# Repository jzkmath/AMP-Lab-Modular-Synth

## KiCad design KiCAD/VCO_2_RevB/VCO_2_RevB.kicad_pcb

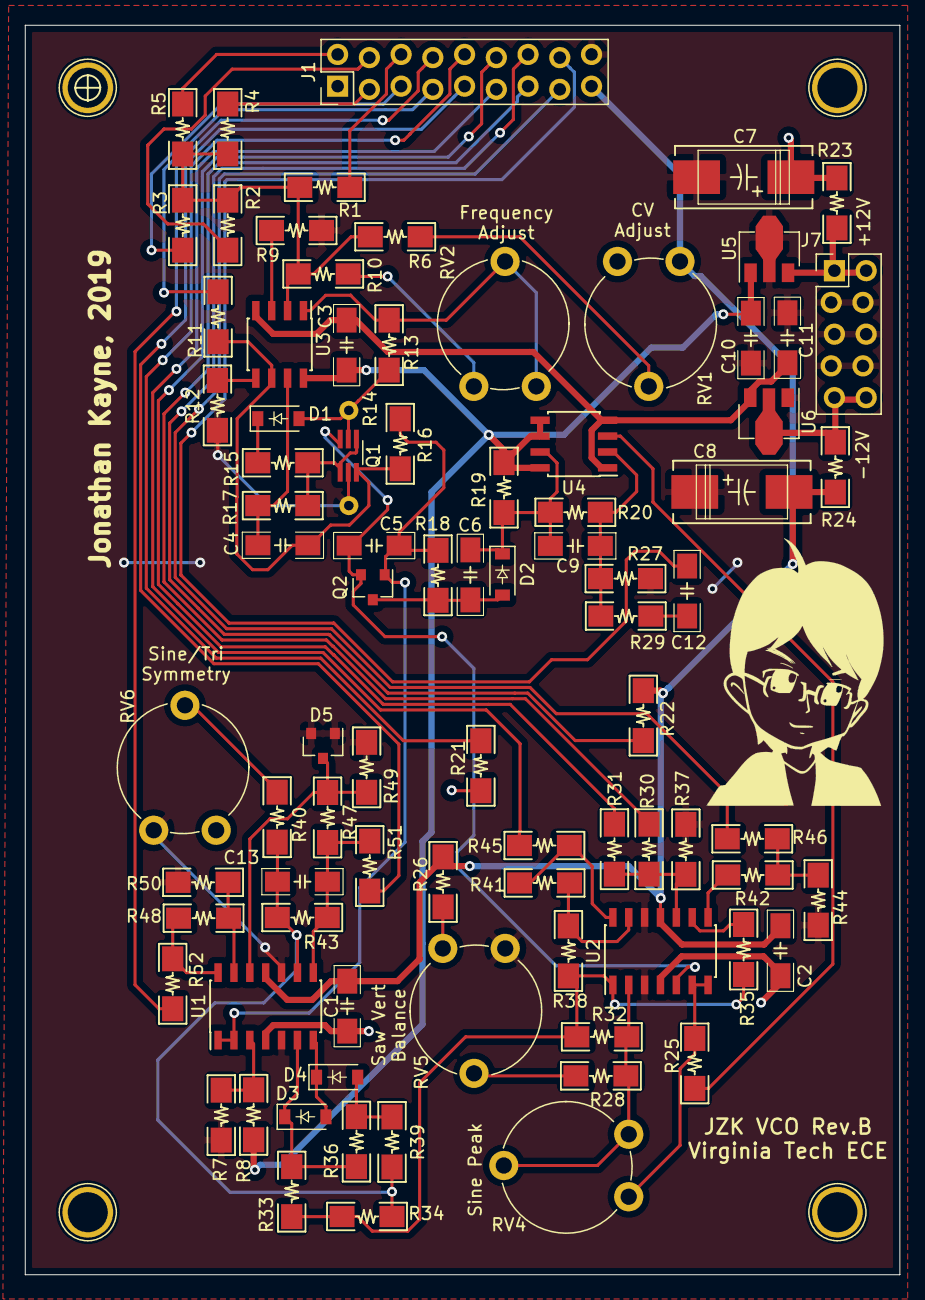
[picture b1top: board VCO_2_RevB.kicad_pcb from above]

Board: 2 copper layers, 70.0 x 100.0 mm, 90 parts (0 on the bottom side), 61 nets.

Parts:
C1, C2, C3, C10, C11: 100nF; C_1206
C4: 100pF; C_1206
C5: 220pF; C_1206
C6, C12, C13: 47pF; C_1206
C7, C8: 22uF; CP_Tantalum_7343
C9: 10pF; C_1206
CN1, CN2, CN3, CN4: M3_Screw; M3_Screw_Hole
D1, D2, D3, D4: 1N4148W; D_SOD-123
D5: BAV99; SOT-23
J1: Interface; PinHeader_2x09_P2.54mm_Vertical_Zigzag
J7: Power; PinHeader_2x05_P2.54mm_Vertical_Zigzag
PHOTO1: ChibiHead
Q1: BC847BS; SOT-363_SC-70-6_Handsoldering
Q2: MMBFJ112; SOT-23
R1, R2, R3, R11, R12, R18, R28, R31, R33, R34, R36, R38, R41: 100k; R_1206
R4: 3.3M; R_1206
R5, R32: 220k; R_1206
R6, R37: 470k; R_1206
R7: 68k; R_1206
R8, R39: 50k; R_1206
R9: 47k; R_1206
R10, R19: 33k; R_1206
R13, R49: 22k; R_1206
R14: 1k Tempco; Tempco_Resistor_SOT363
R15, R16, R20: 1M; R_1206
R17, R25, R27, R29, R35, R42: 10k; R_1206
R21, R22: 7.5k; R_1206
R23, R24: 10; R_1206
R26: 5.6k; R_1206
R30: 180k; R_1206
R40, R47: 150k; R_1206
R43: 200k; R_1206
R44: 4.7k; R_1206
R45, R46, R51, R52: 1k; R_1206
R48: 1.5k; R_1206
R50: 15k; R_1206
RV1: 220k; Potentiometer_Piher_PT-10-V10_Vertical
RV2: 25k; Potentiometer_Piher_PT-10-V10_Vertical
RV4: 100k; Potentiometer_Piher_PT-10-V10_Vertical
RV5: 10k; Potentiometer_Piher_PT-10-V10_Vertical
RV6: 47k; Potentiometer_Piher_PT-10-V10_Vertical
U1, U2: TL074; SOIC-14_3.9x8.7mm_P1.27mm
U3: OPA2137; SOIC-8_3.9x4.9mm_P1.27mm
U4: LM311; SOIC-8_3.9x4.9mm_P1.27mm
U5: L78L12_SOT89; SOT-89-3
U6: L79L12_SOT89; SOT-89-3

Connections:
+12V: C1.1, C2.1, C7.1, J1.1, R21.1, R23.2, RV1.1, RV6.1, U1.4, U2.4
+12VA: C3.1, C10.1, R7.1, R19.1, U3.8, U4.5, U4.6, U4.8, U5.1
+12V_IN: J7.1, J7.2, R23.1, U5.3
-12V: C1.2, C2.2, C8.2, J1.17, R22.2, R24.2, R26.2, RV1.3, U1.11, U2.11
-12VA: C3.2, C11.2, U3.4, U4.1, U4.4, U6.3
-12V_IN: J7.9, J7.10, R24.1, U6.2
CV_Coarse: J1.2, R5.2
CV_Fine: J1.3, R4.2
EXP_CV1: J1.4, R2.2
EXP_CV2: J1.5, R3.2
EXP_FM_CV: J1.6, R1.2
GND: C7.2, C8.1, C10.2, C11.1, D5.1, D5.2, J1.18, J7.3, J7.4, J7.5, J7.6, J7.7, J7.8, Q1.5, R8.2, R9.2, R12.2, R14.2, R27.2, R37.2, R44.2, R48.2, R49.2, RV5.3, RV6.3, U1.5, U1.10, U2.3, U2.12, U5.2, U6.1
Hard_SYNC: C12.2, R29.1
LIN_FM_CV: J1.7, R11.2
unnamed: C4.1, R17.2, U3.7
unnamed: C4.2, Q1.6, R11.1, R16.2, U3.6
unnamed: C5.1, Q2.1, R16.1, R18.2, U1.1, U1.2
unnamed: C5.2, Q1.3, Q2.2, U2.5
unnamed: C6.1, C9.2, D2.1, R19.2, R20.2, U4.7
unnamed: C6.2, D2.2, Q2.3, R18.1
unnamed: C9.1, R20.1, R27.1, R29.2, U4.2
unnamed: C13.1, R43.1, R47.2, R51.2, U1.8
unnamed: C13.2, R34.1, R39.2, R40.2, R43.2, U1.9
unnamed: D1.1, R15.2
unnamed: D1.2, Q1.2, R13.2, R14.1
unnamed: D3.1, R33.1, R36.2, U1.6
unnamed: D3.2, D4.1, U1.7
unnamed: D4.2, R36.1, R39.1
unnamed: D5.3, R47.1, R49.1, U1.12
unnamed: Q1.1, Q1.4, R15.1, R17.1
unnamed: R1.1, R2.1, R3.1, R4.1, R5.1, R6.1, R10.2, U3.2
unnamed: R6.2, RV1.2
unnamed: R7.2, R8.1, U1.3
unnamed: R9.1, U3.3
unnamed: R10.1, RV2.3
unnamed: R12.1, U3.5
unnamed: R13.1, RV2.1, RV2.2, U3.1
unnamed: R25.1, U4.3
unnamed: R25.2, RV4.3, U2.6, U2.7
unnamed: R26.1, RV5.1
unnamed: R28.1, R32.2, RV4.1, RV4.2, U2.2
unnamed: R28.2, RV5.2
unnamed: R30.1, R31.1, R37.1, U2.10
unnamed: R32.1, R33.2, R34.2, R35.2, R38.2, U2.1
unnamed: R35.1, U2.9
unnamed: R38.1, R41.2, U2.13
unnamed: R40.1, RV6.2
unnamed: R41.1, R45.2, U2.14
unnamed: R42.1, R44.1, R46.2
unnamed: R42.2, U2.8
unnamed: R48.1, R50.2, U1.13
unnamed: R50.1, R52.2, U1.14
PW+: J1.10, R21.2
PW-: J1.14, R22.1
PWM_CV: J1.13, R30.2
Pulse: J1.15, R46.1
Pulse_Width: J1.12, R31.2
Sawtooth: J1.11, R45.1
Sine: J1.8, R52.1
Soft_SYNC: C12.1, J1.16
Triangle: J1.9, R51.1

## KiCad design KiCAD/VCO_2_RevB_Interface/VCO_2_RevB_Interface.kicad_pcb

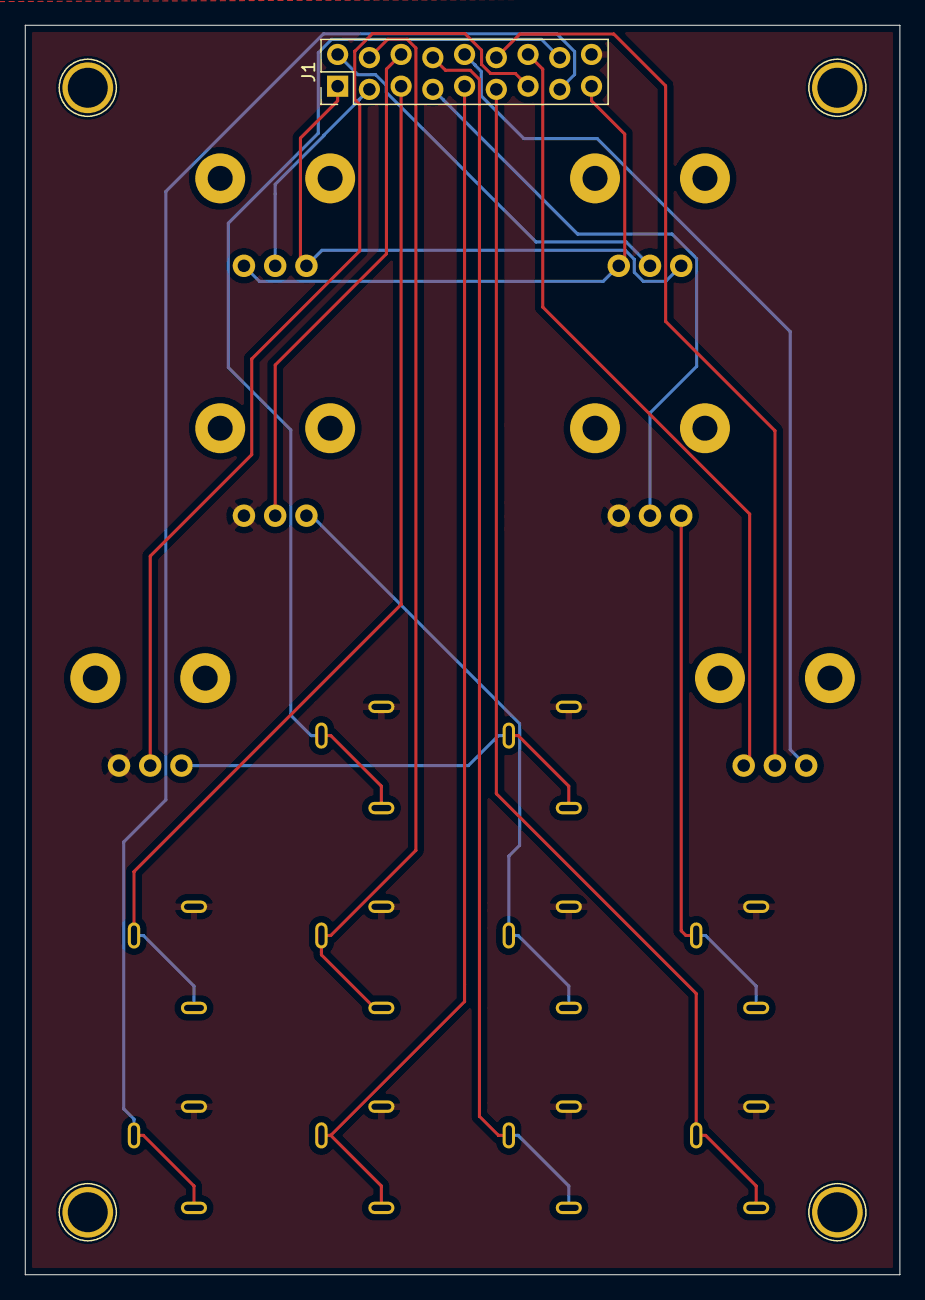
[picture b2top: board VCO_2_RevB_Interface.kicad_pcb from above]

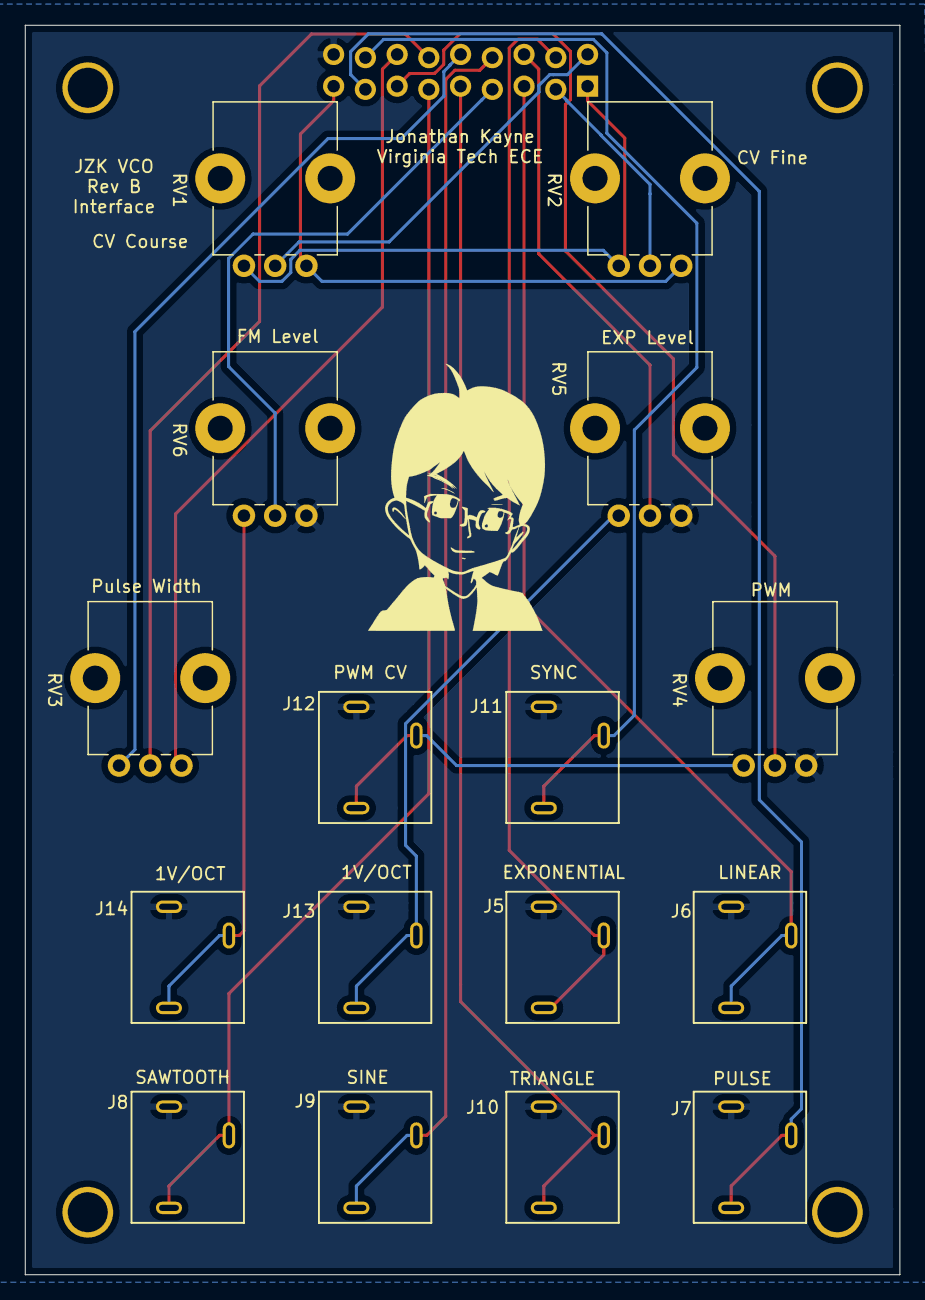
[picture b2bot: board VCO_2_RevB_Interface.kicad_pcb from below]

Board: 2 copper layers, 70.0 x 100.0 mm, 22 parts (17 on the bottom side), 21 nets.

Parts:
CN1, CN2, CN3, CN4: M3_Screw; M3_Screw_Hole
J1: Interface; PinHeader_2x09_P2.54mm_Vertical_Zigzag
J5, J6, J7, J8, J9, J10, J11, J12, J13, J14: 4832; Schurter_4832_Jack
PHOTO1: LOGO; ChibiHead
RV1, RV2, RV3, RV4, RV5, RV6: 25k; Potentiometer_Bourns_PTV09A-1_Single_Vertical

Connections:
+12V: J1.1, RV1.3, RV2.3
-12V: J1.17, RV1.1, RV2.1
CV1: J1.4, J5.2, J5.3
CV2: J1.5, J6.2, J6.3
CV_Coarse: J1.2, RV1.2
CV_Fine: J1.3, RV2.2
EXP_FM_CV: J1.6, RV5.2
GND: J1.18, J5.1, J6.1, J7.1, J8.1, J9.1, J10.1, J11.1, J12.1, J13.1, J14.1, RV4.1, RV5.1, RV6.1
LIN_FM_CV: J1.7, RV6.2
unnamed: J12.2, J12.3, RV4.3
unnamed: J13.2, J13.3, RV5.3
unnamed: J14.2, J14.3, RV6.3
PW+: J1.10, RV3.3
PW-: J1.14, RV3.1
PWM_CV: J1.13, RV4.2
Pulse: J1.15, J7.2, J7.3
Pulse_Width: J1.12, RV3.2
Sawtooth: J1.11, J8.2, J8.3
Sine: J1.8, J9.2, J9.3
Sync: J1.16, J11.2, J11.3
Triangle: J1.9, J10.2, J10.3
